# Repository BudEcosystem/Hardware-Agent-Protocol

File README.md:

# Bud Hardware Model Standard

An independent research and design project for agents operating physical devices, from tiny microcontrollers and microscope retrofits to instrument fleets and industrial cells. Intended agent host: the adjacent `Bud-Meta-Harness` repository. This project is **not an implementation of Anthropic's unpublished MHS specification**.

## BHMS: the protocol, SDKs and tools

BHMS (Bud HMS, protocol version `2026-11-15`, with `2026-11-13` compatibility) is the protocol this research produced: JSON-RPC 2.0 in the shape of MCP,
for AI agents, programs and people that discover, observe and operate physical devices, with durable idempotent
operations, honest evidence labels, leases with fencing, unknown outcomes that are never guessed, and a stop that never
waits. It is tested against simulated devices and host-built firmware; no physical device has been validated yet.

- **Start here:** [developer documentation](docs/bhms/index.md), [quickstart](docs/bhms/quickstart.md) (a device server,
  Claude through MCP, an OpenAI model, a gateway; every step executed by the test suite), [concepts](docs/bhms/concepts.md).
- **Specification:** [`spec/bhms`](spec/bhms/README.md) (chapters 01 to 15, JSON Schema, examples, conformance index).
- **Code:** Python SDK, gateway, agent bridges and conformance runner in [`sdk/python`](sdk/python/pyproject.toml)
  (`pip install -e 'sdk/python[mcp,openai]'`, then `bhms --help`); [`sdk/typescript`](sdk/typescript/README.md);
  the C library and Arduino wrapper for microcontrollers in [`sdk/c`](sdk/c/README.md); SimLab, a simulated laboratory
  with real-protocol instruments, in [`simlab`](simlab/README.md); the open BHMS Arm in [`hardware/actuator`](hardware/actuator/README.md).
- **Changes and numbers:** [migration notes](docs/bhms/migration.md), [performance](docs/bhms/performance.md),
  [final validation report](docs/bhms/validation-report.md).

The rest of this README describes the earlier HMS research runtime (`hms/`, `protocol/`, `tests/`) and its retained
evidence.

**Current status:** the executable local simulation runtime combines the registry, admission policy, durable journal, checked API/SDK and `hctl` CLI. A native Harness overlay exercises real tool/PTC calls at a pinned commit in an isolated checkout, with full artifact and aggregate builds passing. A local MCP projection supports current and legacy clients over stdio. The runtime can mount multiple local and compact C simulation routes under one authority, with immutable operation routing, durable mappings, receipt reconciliation and host-process recovery. An explicitly selected shared-board GPIO/PWM simulation also uses the same public tools and resource admission. Primary-source research and checked WoT descriptions support the design. Real adapters, complete commissioned firmware, production Harness integration and physical validation remain unfinished. [Progress and requirement audit](PROGRESS.md) records the evidence and remaining work.

The [qualification libraries are installed in the main project](artifacts/implementation/runtime-qualification-package/README.md):
40 additional host modules and 42 package files retain the exact qualified source.
The installed identity inspection matches the successful candidate, including its
267-file worker image. A new full public run passes **866 tests**, preserving all
861 prior tests and adding five original vault commit checks, with **244 stable
inputs** including native C and binary files. [Library guide](docs/qualification-libraries.md).
Public qualification/PAT service mounting, prompt learning and physical providers
remain unfinished; the native supervisor retains its explicit host/ABI profile.

An isolated [intent handoff](artifacts/implementation/prompt-intent-handoff/README.md)
now retains natural-language intent revisions and checked agent proposals, with
22 focused tests passing. It preserves exact replay and refuses stale proposals;
it does not qualify, promote or execute them. The [source audit](artifacts/design/prompt-intent-handoff/README.md)
records the remaining learning/qualification and Harness integration gaps.

The [selection-reuse host candidate](artifacts/implementation/standing-host-selection-reuse/RESULTS.md)
passes 34 compiler comparisons and nine native management/freshness cases.
Private compilation reuses one freshly validated snapshot within the call,
reducing installation validations from five to one while preserving current
authority and final guards. Its [subsequent full-capacity attempt](artifacts/implementation/standing-host-selection-capacity/RESULTS.md)
still hits the thirty-second limit, retaining 110 settled and one prepared START.
Full capacity and performance benefit remain open.
The [phase-kernel firmware](artifacts/implementation/standing-endpoint-phase-kernels/RESULTS.md)
passes six complete differential traces and saves another 716 flash bytes.
Its failed link charges 39,186 flash bytes, exceeding the original AVR application
allowance by 6,930 bytes; no valid target image or complete stack proof exists.

The isolated [Arduino runtime integration](artifacts/implementation/avr-link-integration/README.md)
joins the finite endpoint, serial receive/transmit, Timer1 and durable boot
reservation. Eleven integrated register-model cases pass normally and under
ASan/UBSan, alongside the original endpoint suite. The combined ATmega328P image
cross-links at 21,778 flash bytes and 1,343 static SRAM bytes. These are model
and build results; target execution, physical I/O and persistent applications
remain unfinished.

The isolated [compact-bitmap storage candidate](artifacts/implementation/compact-bitmap-store/README.md)
passes 329 focused checks and a paired 426-operation screen while preserving
current identity checks and full durability barriers. Its full 4,270-file writer
still times out at the original 180-second limit. A read-only audit verifies
35 retained images, including 1,814 complete files and all 169 directories in
the interrupted writer. The candidate remains unadopted; all 244 public inputs
retain the existing 866-test baseline. The preceding
[attribution](artifacts/verification/full-storage-attribution/README.md) and new
[existing-state overwrite review](artifacts/verification/state-overwrite-hypothesis/README.md)
retain the evidence and next hypothesis. An [existing-state replacement draft](artifacts/implementation/existing-state-replacement/STATUS.md)
has source only; its delegated preparation was stopped by automatic review and
no model or replay was executed.

Device I/O, drivers and the intelligence hub share one
[managed resource graph](docs/io-driver-hub-control.md) and an explicit
[I/O and driver boundary](spec/12-io-driver-boundary.md). New acquisition,
configuration and native queue handoff retain their actual effects and authority.
The isolated
[hub recovery increment](artifacts/implementation/owned-hub-recovery/RESULTS-REVIEW.md)
passes five groups covering interrupted terminal writes, retained handles,
typed computation, replay and limits. A separate [owner-death harness](artifacts/implementation/owned-hub-crash-harness/README.md)
passes twelve actual process-death checkpoints, preserving six not_started,
three unknown and three completed outcomes without relaunching historical work.
The [writer-deferral controls](artifacts/implementation/owned-hub-writer-deferral/RESULTS-REVIEW.md)
add three deliberate held-writer cases after leader exit and owner death. Recovery
retains admission until the writer settles, then records unknown; independent
auditing verifies the retained rows, leases and all ten controlled process reaps.
It is not yet a public mount or a qualified GB10/GPU/driver/device provider.

The [standing endpoint design](artifacts/design/standing-endpoint-programs/README.md)
specifies local triggers, feedback, renewable authority, retained evidence and
shared I/O ownership for a narrow Arduino controller. The [fit candidate](artifacts/implementation/standing-endpoint-fit/RESULTS-REVIEW.md)
passes thirteen native cases / 673 assertions in both normal and sanitizer builds,
plus the finite endpoint and runtime regressions. It reduces flash load by 582
bytes and meets the 160-byte static-growth allowance. Its ATmega328P link still
fails: 43,064 flash-load bytes exceed physical flash by 10,296 bytes.
Target fit, complete learning, installation and physical qualification remain
unfinished. The [prompt-to-PAT contract](docs/prompt-to-pat.md) keeps planning,
perception and evidence failures distinct.

The subsequent [LTO profile](artifacts/implementation/standing-endpoint-lto/RESULTS-REVIEW.md)
compiles all twelve units but still fails linking: **41,892 flash-load bytes**,
or **9,124 bytes over physical flash**. Static SRAM remains 1,503 bytes. The
1,172-byte reduction includes a stronger explicit symbol-retention policy.
Both attempts and 32 command reaps are audited; no valid ELF or final combined
stack/timing proof exists. The unchanged native source retains its parent tests.

The [copy/boundary successor](artifacts/implementation/standing-endpoint-copy-boundary/RESULTS-REVIEW.md)
passes fourteen standing cases / 766 assertions in normal and sanitizer builds,
plus the finite/runtime regressions. Flash load is now 41,810 bytes, still 9,042
over physical flash. Its generated standing branch retains six caller bytes
instead of 101; complete stack/ISR analysis and target fit remain open.
The subsequent [shared-kernel refactor](artifacts/implementation/standing-endpoint-shared-kernel/RESULTS.md)
implements shared time/serialization work across both protocols. Four complete
baseline/candidate traces match, including 475 new boundary assertions; numeric
controls pass 13,014 assertions in each mode. Flash load falls by 1,908 bytes to
39,902, still 7,134 above physical flash. All 50 command reaps are audited.
There is no valid target ELF or complete stack/timing qualification.

The [host deployment integration plan](artifacts/design/standing-host-deployment/HOST-DEPLOYMENT-PLAN.md)
maps the remaining journal, shared ownership, version-2 transport, durable
commit-before-ACK collection and standing PAT work to existing source. Its isolated
implementation now passes [twenty native host cases / 173 checks](artifacts/implementation/standing-host-deployment/RESULTS-REVIEW.md).
It includes one shared finite/standing authority, an original-evaluator-backed
literal PAT path and a 16 MiB all-writer logical partition. Prepared-only recovery,
durable reply disputes, policy replacement and separate REVOKE uncertainty have
controls. A separate [thirteen-cut owner-death increment](artifacts/implementation/standing-host-owner-death/RESULTS-REVIEW.md)
now passes with the native endpoint surviving each killed host. Historical
possible effects are not resent, and exact terminal evidence gates claim release.
The [boundary successor](artifacts/implementation/standing-host-boundaries/RESULTS.md)
adds eight authority/replay and ten synchronous storage-failure controls that
pass. Its mutation-capacity attempt reaches the unchanged 30-second wall limit
after 68 never-handed-off mutations; the failed attempt is retained and the
remaining matrix is unexecuted. Full capacity, broader failure modes, public mounting and physical drivers remain
open; these results are partial validation of the fixed synthetic profile.

The [PAT foundation](artifacts/implementation/runtime-pat-foundation/README.md)
provides commit-time validation, compiler identity and static resource checks.
The new [statement-cache integration](artifacts/implementation/pat-statement-cache/README.md)
passes **nineteen catalog controls and the complete thirty-case worker → vault →
catalog → PAT application flow**. One simulated application completes once, with
original-key replay, configuration drift refusal and cold history intact.

The worker completes in about 57.7 seconds under the original 60-second limit;
the parent completes in 141.1 seconds under 180 seconds. The only production
change is a 256-statement authority Journal cache. That same edit is now in the
public runtime, where the preceding full run passed **861 tests** with 161
stable inputs. The subsequent library installation above extends that coverage.
Public qualification, prompt learning and physical device/driver/hub providers
remain unfinished. One successful local run does not qualify deployment timing.

The preceding [local comparison](artifacts/verification/pat-statement-cache-evaluation/README.md)
passes 62 checks and observes 38.46% lower median capture CPU; this is not a
whole-worker speedup claim. The [binding review](research/host-contract/sqlite-cache-binding/README.md)
adds 4,025 fully read LF lines and records cursor/memory lifetime constraints.

The [current worker diagnostic](artifacts/verification/qualification-current-profile/README.md)
retains a complete-matrix request and the original limits. It stops at the deadline
with 21 case manifests, records current SQLite/validation/durability costs and
publishes no qualification or application. A separate encoder experiment passes
1,875 semantic cases but is not adopted because its timing benefit is inconsistent.
The subsequent [SQL metadata experiment](artifacts/verification/pat-sql-metadata-evaluation/README.md)
matches 410 differential cases but is also unadopted: fewer queries produce about
6.3% higher median CPU in the fixed local comparison. The
[statement-cache review](research/host-contract/sqlite-statement-cache/README.md)
adds 477 fully read LF lines and identifies a separate hypothesis to measure:
164 distinct authority capture statements versus the installed 128-statement
default. This static count does not establish cache misses or a timeout cause.

The [qualification package candidate](artifacts/implementation/qualification-package/README.md)
has explicit package imports and a pinned worker image. Import and identity checks
pass, but its actual thirty-case qualification hit the original worker deadline:
25 case manifests were retained, with no evidence publication or PAT application.
The failure is preserved separately from catalog controls; public integration
remains unfinished. That failed attempt remains retained; the later cache candidate above completes the same matrix.

The earlier isolated [authority-vault catalog](artifacts/implementation/pat-vault-catalog/README.md)
passes 19 controls and the complete thirty-case worker → vault → catalog → PAT
application flow. One simulated GPIO application completes exactly once; original-key
history survives configuration drift and cold vault/bridge reconstruction. Complete
candidate evidence and current device/driver applicability are checked through
admission commit. Public integration, prompt learning and physical device, driver
and intelligence-hub providers remain unfinished.

The preceding isolated [vault batch candidate](artifacts/implementation/pat-vault-batch/README.md)
passes 60 controls for complete bounded evidence views and their admission-commit
checks. Missing batch members refuse the view; expiry rolls back admission, while
post-commit lease failure retains original-key replay. Its distinct catalog mount
is now connected in the isolated profile above; the full learning loop and physical
providers remain unfinished.

The preceding isolated [business commit candidate](artifacts/implementation/pat-business-precommit/README.md)
passes 51 controls for final evidence checks, rollback, clock-floor preservation
and original-key replay after lost commit replies. It adds the transaction boundary
needed by the independent evidence vault; the bounded catalog evidence view,
public integration and physical providers remain unfinished.

Durable ordered procedures coordinate those routes with atomic child admission,
explicit restart continuation and checked CLI/MCP access. The latest full run
passes **861 tests**, with all 161 inputs and compiler identity unchanged.
The previous 748-test result remains an immutable historical baseline.
The earlier 747-test run retains its status-read timeout. A controlled reproduction
and five passing transport tests verify the test-only polling correction within
the original deadline, without mutation retries. Earlier passing and failed runs
remain preserved. The new
[PAT simulation qualification components](docs/pat-simulation-qualification.md)
include closed configuration/domain contracts, shared environment extraction,
an executable isolated fan worker, a catalog evidence gate and a bounded evidence
reducer/store. The corrected store/hook integration passes 46 focused tests with
fresh worker outputs. Later isolated durable supervision and recorded I/O catalog
integration are verified below; the public qualification service remains unfinished.
The pure I/O resource topology library now passes 21 focused tests;
resource admission and the evidence memo are now integrated as libraries, with
corrected compiler dependency identity. Their focused checks pass 32 and 77 tests;
the new full runtime check includes these libraries alongside the topology,
evidence store and evaluation-integrity fixes. A separate synthetic GPIO/PWM
provider is now [mounted through the public tools](docs/io-simulation.md).
Its final four real CLI/MCP transport cases pass after retained failed37 and
failed52 attempts exposed two integration defects and an incorrect resume-test
expectation. Physical providers and executed driver/hub lifecycle control remain
further work.
[Typed PAT compilation and a trusted local promotion catalog](docs/pat-foundation.md)
and [deterministic selection with atomic instances](docs/pat-execution.md)
now extend that foundation as host libraries. A targeted
[compact admission refresh](docs/compact-admission-refresh.md) addresses reproduced
presence expiry without changing the original request bounds; all 25 focused
admission tests pass within that full run. Prompt-driven applications that learn into deterministic
Programs as Tools, and control spanning device I/O, drivers and intelligence-hub
resources, are core requirements with explicit designs; their full implementation
and physical qualification remain open. Historical Harness runs retain their
exact earlier runtime snapshots.

The isolated [recorded I/O catalog integration](artifacts/implementation/pat-io-definition-build/README.md)
passes 21 pure controls and the actual complete 30-case worker/import/catalog/PAT
application/replay scope. Original-key replay adds no effect, configuration drift
refuses fresh reuse, and cold historical replay survives a session change. Earlier
failed scopes remain preserved. Protected control capacity and public mounting
remain unfinished; this is simulated-device evidence.

The [control-storage review](docs/control-storage.md) adds five passing bounded
SQLite experiments and an unchanged-state allocation audit. It specifies separate
evidence/control storage and capacity owed to admitted work. The corresponding
production profile and actual capacity provider remain to be implemented.

An isolated [immutable evidence vault](artifacts/implementation/pat-evidence-vault/README.md)
now preserves the complete retained I/O dataset in a separately capped database.
All 22 distinct methods have passing receipts on identical production code, with
startup and test-assertion failures retained. An [authority-publication candidate](artifacts/implementation/pat-vault-authority/README.md)
now binds that vault to an actual runtime authority and records original import
intents and manifest references. All [25 selected current-production controls](artifacts/verification/pat-vault-authority-controls/README.md)
now pass in separate scopes, with interrupted attempts and the earlier aggregate
failure retained. Actual-run validation through this profile, catalog integration,
public mounting and backed control capacity remain unfinished.
The [fresh actual trial](artifacts/implementation/pat-vault-original-run/README.md)
hit its original worker deadline before import; its partial capture and unknown
worker outcome remain retained for diagnosis.

A [bounded current-worker profile](artifacts/verification/pat-vault-worker-profile/README.md)
now identifies repeated validation/serialization work for evaluation. Its own
original scope also stopped at the unchanged deadline; all retained bytes and
source databases pass the read-only audit. It establishes neither a timeout cause
nor a complete import, and introduces no production change.

A [pure validator evaluation](artifacts/verification/pat-validation-walk-evaluation/README.md)
passes 468 differential cases. Its small, inconsistent timing improvement is
insufficient to adopt it as a deadline correction; production stays unchanged.

The subsequent [one-call topology/proof candidate](artifacts/implementation/pat-io-proof-batch/README.md)
passes 63 pure controls and reduces repeated validation in definition building.
Its full actual trial still reaches the unchanged worker deadline before import;
it remains isolated and does not qualify the end-to-end path. Original results and
verified retained copies are preserved, including the later loss of temporary trees.

A [whole-worker accounting diagnostic](artifacts/verification/pat-worker-accounting/README.md)
now separates parent and child resource use without changing the project or worker
code. Fifteen observer controls pass. The actual scope still reaches the original
deadline with 25 retained case manifests and no import. During its roughly
60-second worker interval, parent and child use 18.45 and 36.58 CPU seconds.
The audit verifies all retained bytes and original launch association; the next
investigation is parent monitoring cost, with no established single timeout cause.

The [retention-scan comparison](artifacts/verification/pat-retention-scan-cost/README.md)
now verifies 72 read-only scans of the original retained tree. A separate
[native host prototype](artifacts/verification/pat-native-retention-prototype/README.md)
passes 20 differential controls and five syscall scopes, with roughly 61% lower
median scan CPU time in fixed local pairs. Original metadata remains unchanged.
The helper is not integrated; full worker/import qualification remains required.

The subsequent [in-process native binding](artifacts/verification/pat-native-retention-binding/README.md)
passes 43 production-build controls, 20 separate instrumented controls and three
actual syscall scopes. It preserves signal exceptions and descriptor cleanup and
adds opened-directory identity checks. It remains isolated, with no new whole-worker
performance or qualification result. Physical I/O, driver and hub providers remain
required parts of the system.

The [isolated supervisor integration](artifacts/implementation/pat-native-supervisor/README.md)
now loads the verified scanner through a sealed memory image. Six loader scopes
and sixteen audit-guard controls pass. The complete actual worker still reaches
its original deadline before import, leaving fifteen manifests and interrupted
effects unknown. All retained state and source identities are verified; no
whole-worker speedup, public adoption or complete PAT qualification is claimed.

The subsequent [native worker accounting diagnostic](artifacts/verification/pat-native-worker-accounting/README.md)
passes 21 pure controls with unchanged project code. Its full trial reaches the
original deadline with twenty-nine manifests and no import. It measures 10.79
supervisor and 35.85 worker CPU seconds, and verifies the original launch and all
retained state without opening interrupted case databases. Qualification remains
failed; exact canonical-serialization evaluation is the next proposed improvement.
Four previously partial API texts are now fully read in a retained overlay.

The latest [guarded canonicalization candidate](artifacts/implementation/pat-integer-canonical/README.md)
passes the **complete original thirty-case worker and authority-vault import**,
including original-key replay and cold-vault history after configuration drift,
within the unchanged limits. It passes 1,668 pure differential cases and nine
public contract tests. The read-only audit verifies every retained vault body and
its original association. This remains an isolated simulation candidate; the
distinct vault catalog profile, public mounting and backed capacity are next.

## Start here

- [Scope and completion requirements](spec/00-scope.md)
- [Architecture and foundational command interface](spec/01-architecture.md)
- [Execution, state, cancellation and recovery semantics](spec/02-execution.md)
- [Registry, tool manager, runtime and performance](spec/03-registry-runtime.md)
- [Home, scientific and manufacturing scenarios](spec/04-scenarios.md)
- [WoT description profile and execution boundary](spec/05-description-profile.md)
- [Workflow, material identity and recovery](spec/06-workflows-materials.md)
- [Constrained endpoint binding](spec/07-constrained-binding.md) and [serial codec](protocol/serial/README.md)
- [Host invocation, identity and durable journal profile](spec/08-host-contract.md)
- [Local registry and simulation runtime](spec/09-local-runtime.md) and [runnable CLI walkthrough](docs/local-control.md)
- [Checked local API contracts and SDK](spec/10-local-api-contracts.md)
- [Experimental compact endpoint wire/state profile](spec/11-endpoint-wire.md) and [implementation/verification](protocol/endpoint/README.md)
- [Device I/O, driver lifecycle and intelligence-hub boundary](spec/12-io-driver-boundary.md)
- [Durable compact host binding and recovery](docs/compact-host-binding.md)
- [Multiple installed simulation adapters](docs/multi-adapter-runtime.md)
- [Shared-board GPIO/PWM simulation and startup](docs/io-simulation.md)
- [Local MCP tools and interoperability evidence](docs/mcp-integration.md)
- [Platform primitives and finite boot reservations](protocol/platform/README.md)
- [Microscope knob retrofit](docs/microscope-retrofit.md)
- [Bud Meta Harness integration](docs/harness-integration.md)
- [Native Harness overlay and frozen 315-test runtime verification](integration/harness/multi-adapter/README.md)
- [Conformance and physical validation plan](docs/conformance-plan.md)

## Research

- [Official MHS source findings and independent implementation critique](research/mhs/notes/findings.md)
- [Protocol landscape](docs/protocol-landscape.md) and [corpus notes](research/protocols/README.md)
- [WoT reuse decision](docs/wot-reuse-decision.md) and [MQTT/Sparkplug binding requirements](docs/transport-guarantees.md)
- [Physical-AI architectures](docs/physical-ai-landscape.md) and [reading notes](research/physical-ai/notes/reading-notes.md)
- [Learned-control deployment profile](docs/learned-control-profile.md) and [GR00T/OpenVLA full review](research/physical-ai/notes/vla-full-review.md)
- [Laboratory corpus](research/laboratory/README.md) and [SiLA/Bluesky/LabOP binding requirements](docs/laboratory-bindings.md)
- [Description/profile review and repairs](docs/profile-review.md)
- [Constrained protocol corpus](research/constrained/README.md) and [embedded implementation evidence](docs/embedded-evidence.md)
- [Planning and skill grounding](docs/planning-and-grounding.md), [planning corpus](research/planning/README.md), and [Modbus/SCPI bindings](docs/instrumentation-bindings.md)
- [Prompt-to-PAT learning and deterministic reuse](docs/prompt-to-pat.md), [bounded procedures](docs/bounded-procedures.md), and [device I/O, driver and hub control](docs/io-driver-hub-control.md)
- [Executable PAT qualification components and their limits](docs/pat-simulation-qualification.md)
- [Host persistence evidence](research/host-contract/README.md) and [AVR target build/UART review](research/constrained/avr/notes/target-build-and-uart-review.md)
- [Home Assistant/ESPHome binding evidence](docs/home-bindings.md), [OSCORE security binding](docs/oscore-binding.md), and [EDHOC full review](docs/edhoc-binding.md)
- [Observe/Blockwise/reliable-CoAP analysis](docs/coap-streaming-binding.md), [feedback and spatial planning](docs/planning-continuation.md), and [local timing measurements](docs/local-performance.md)
- [OPC UA industrial binding review](docs/opcua-binding.md) and [MCP specification corpus](research/mcp/README.md)
- [Current LwM2M Core/Transport review](docs/lwm2m-current-binding.md) and [microscope controller evidence](docs/microscope-controller-binding.md)
- [WoT Architecture full reading and binding analysis](docs/wot-architecture-binding.md)
- [AVR/RP2040 clock, boot and storage evidence](docs/clock-boot-platform.md)
- [Original AVR Timer1 clock implementation and checks](docs/avr-clock-implementation.md), and [full Q-Block review](docs/qblock-binding.md)
- [GB10/DGX Spark hub deployment evidence](docs/gb10-deployment-evidence.md)
- [Search and full-reading backlog](research/PLAN.md)

Raw articles, papers and pinned source checkouts/snapshots are local under `research/`. Acquisition manifests and reading logs are separate: downloaded is not synonymous with read. Source licenses remain with their owners. The small audited JCS library is intentionally [vendored](hms/_vendor/README.md); other research checkouts are reference material. Large model weights, training datasets, recursive submodules and complete Git history have not been acquired.

## Check the draft artifacts

Python 3, `requests`, `beautifulsoup4` and `jsonschema` are used by the local research utilities. The complete Python test suite additionally uses installed MCP SDK 1.26.0 and AnyIO as tester dependencies; the production MCP projection does not depend on that SDK. Native C framing tests additionally require GCC; the stress check uses address/undefined-behavior sanitizers. PDF extraction uses `pdftotext`. These were available in the working environment; reproducible dependency locking is still outstanding.

```sh
python3 scripts/audit_corpus.py
python3 scripts/check_descriptions.py
python3 scripts/check_wot_profile.py
python3 scripts/check_endpoint_scenarios.py
python3 -m unittest discover -s tests -v
python3 scripts/check_serial_native.py
python3 scripts/check_endpoint_native.py
python3 scripts/check_endpoint_integration.py
python3 scripts/check_compact_mcp.py
python3 scripts/check_boot_epoch.py
python3 scripts/check_avr_eeprom.py
python3 scripts/check_host_journal.py
python3 scripts/check_runtime.py
```

The JSON descriptions in `examples/` and `examples/wot/` are synthetic, uncommissioned design examples. WoT TD 1.1 is the chosen host description direction; the action forms now project the full host envelope. Static fixtures pin their original physical-contract files, while executable simulation types use a separately versioned type-bundle digest. Example HTTPS forms are placeholders, not installed endpoints. The CLI uses an authenticated local Unix socket; all processes with one Unix UID share a principal. Checks cover corpus integrity, descriptions, framing, request identity, simulated execution and crash recovery. They do not establish physical behavior, timing or complete protocol conformance. The [AVR build instructions](research/constrained/avr/notes/target-build-and-uart-review.md) reproduce its component-only footprint without flashing hardware.

The [endpoint build](protocol/endpoint/README.md) additionally cross-links the executor, framing and synthetic callbacks for ATmega328P. Its 15,780-byte flash image, 1,335-byte static RAM allocation and conservative static stack analysis fit the declared planning reservations; no target program ran. Qualified clock/NVM/UART and actual device drivers remain separate work. [Evidence consistency audit](artifacts/verification/endpoint-evidence-audit.json) links the retained source, binary and test receipts.

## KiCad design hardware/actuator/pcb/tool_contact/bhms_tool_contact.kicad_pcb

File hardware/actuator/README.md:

# BHMS Arm — universal actuator hardware

BHMS Arm is a 5-axis desktop arm built from Feetech STS3215 12 V serial
bus servos. It has a quick-change tool flange and four end effectors:

* parallel gripper
* compliant knob turner with an output encoder
* button presser with a force-sensing tip
* slider/rocker pusher

An RP2040 controller board drives the arm. A hardware E-stop cuts the
servo power with no firmware involvement. The arm is the physical
counterpart of the SimLab arm twin: `sim/bhms_arm.xml` is generated from
the same parameters and CAD solids that produce the printed parts.

**Status.** Design only (Task 13a). Nothing has been printed, assembled,
powered or certified, and no PCB has been manufactured.

* CAD, MJCF and PCBs are checked by tools: OpenCASCADE, trimesh, MuJoCo
  4.0.1, KiCad 10.0.6 `kicad-cli`, Freerouting 1.9.0 and the scripted
  checks in this tree. Results are in `docs/design.md` §10.
* Both PCBs are fully routed (the controller needed a scripted completion
  pass after the autorouter, `pcb/finish.py`) with 0 KiCad ERC/DRC errors.
  They have not been reviewed by a person: read `docs/design.md` §12 (O7)
  before ordering. `pcb/build.py fab` refuses to write Gerbers for any
  board that has known open routing (`pcb/<board>/known_open.json`) and
  writes `DO_NOT_FABRICATE.md` instead.
* The arm falls when the E-stop cuts power (no brake): `docs/design.md` §9.
* Firmware (Task 13b): `firmware/` (README.md). Its contract is `firmware/INTERFACE.md`.

| | |
|---|---|
| Reach (shoulder axis → flange) | 400 mm (180 + 140 + 80) |
| Rated load | 250 g carried object, tool excluded, 70 mm beyond the flange, plus the 159 g gripper. Static 2× margin against the enforced servo torque limits at every joint (shoulder 2.06× at its 78 % limit, elbow 3.62×, wrist 4.64×); machined steel shoulder pinion |
| Joints | yaw ±150°, shoulder −20…+95° (3:1), elbow −5…+125° (2:1), wrist pitch ±100°, wrist roll ±150°, plus coupled pitch limits (shoulder+elbow ≤ 175°, elbow+wrist ≤ 165°, sum of all three ≤ 183°; `firmware/INTERFACE.md` §3.2) |
| Tool flange | 3-lug bayonet locked by a +30° wrist roll; 6 pogo contacts: 12 V, GND, bus, AUX1, AUX2, tool ID |
| Controller | RP2040, 16 MB flash, USB-C, 12 V in with fuse/TVS/reverse protection, half-duplex servo bus, INA219 rail sensing, hardware E-stop loop, tool port, RGB LED, SWD |
| Cost (estimate) | see `bom/bom.csv` totals |

## Layout

```
params.py lives in cad/ — every dimension, ratio, limit, servo ID and tool ID
cad/            build123d part modules (cad/parts/*.py), build.py, mesh/clearance/torque checks
cad/out/        STL (committed, each < 2 MiB), STEP (manifest only), parts/assembly/check JSON
sim/            gen_mjcf.py -> bhms_arm*.xml, scene_pick.xml; test_arm.py; results/sim_results.json
pcb/            controller.py, tool_contact.py (circuits + placement), KiCad writers, router glue, DRC
pcb/<board>/    .kicad_sch/.kicad_pcb/.kicad_pro (KiCad 8 format), netlist, reports, fab/ (Gerber, drill, pos)
bom/            build_bom.py -> bom.csv
firmware/       RP2040 firmware: portable core, host simulator and tests, pico-sdk port; INTERFACE.md is the contract
docs/           design.md (requirements, torque budget, safety, decisions), assembly.md, img/
verify.sh       regenerate + verify everything
```

## Regenerate

The worker used for verification had build123d 0.13 / OCP 8.0.1 and
trimesh 5.2 in one venv, MuJoCo 4.0.1 in another, and KiCad 10.0.6
unpacked from the Ubuntu .debs:

```bash
CAD_PY=~/venvs/cad/bin/python SIM_PY=~/venvs/arm/bin/python \
FREEROUTING="xvfb-run -a java -jar freerouting-1.9.0.jar" ./verify.sh
```

With `FREEROUTING` unset (or `SKIP_ROUTE=1`) `verify.sh` imports the
committed Freerouting sessions (`pcb/*/*.ses`) instead of re-routing, which
reproduces the committed boards exactly. A missing `kicad-cli` fails the
run unless `ALLOW_NO_KICAD=1` is set; then the KiCad ERC/DRC/Gerber steps
are reported as SKIPPED in the summary. The interference check uses
`CLEARANCE_JOBS` worker processes (default 6) and takes about 10 minutes.

Each step is also a plain script: `cad/build.py`, `cad/check_meshes.py`,
`cad/check_clearance.py`, `cad/torque_budget.py`, `sim/gen_mjcf.py`,
`sim/test_arm.py`, `pcb/build.py {generate,route,check,fab}` and
`bom/build_bom.py`.

## Using the twin in SimLab

Load `sim/bhms_arm.xml`; it has the gripper. Variants `bhms_arm_<tool>.xml`
carry the other tools. Actuator, joint and sensor names match the
firmware's joint names (`base_yaw`, `shoulder_pitch`, …). Tool TCPs are the
`tcp` site. Keyframe `home` (yaw 0°, shoulder 30°, elbow 90°, wrist 45°, roll 0°) is the pose the
controller reaches after calibration and the rest pose for a normal stop; it satisfies
all joint and coupled limits.

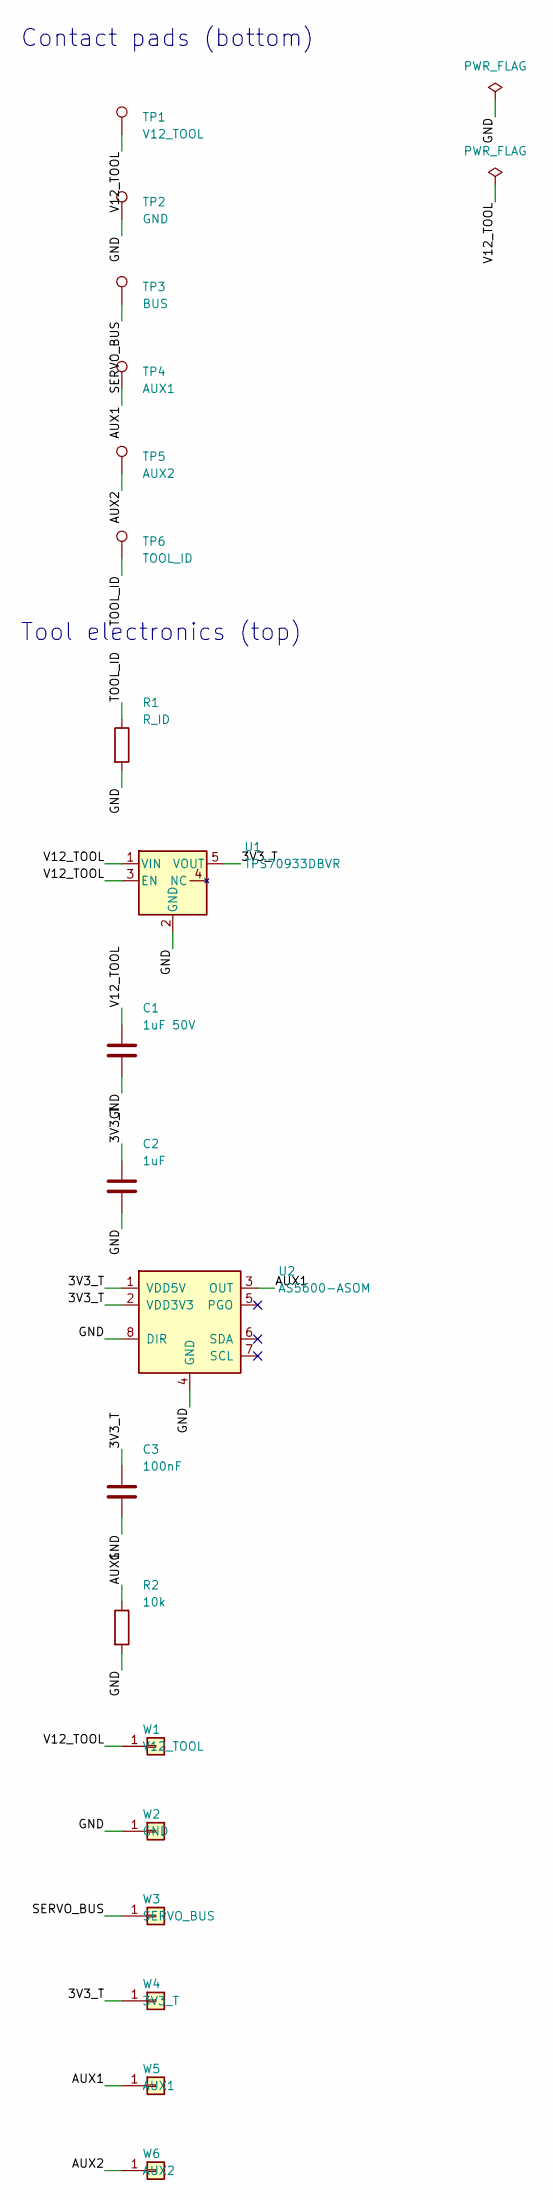
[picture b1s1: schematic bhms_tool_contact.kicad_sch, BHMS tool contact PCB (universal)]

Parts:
C1: 1uF 50V; C_0603_1608Metric; MPN GRM188R61H105KAAL
C2: 1uF; C_0603_1608Metric; MPN GRM188R61H105KAAL
C3: 100nF; C_0603_1608Metric; MPN CL10B104KB8NNNC
R1: R_ID; R_0603_1608Metric; MPN RC0603FR-07xxxL (per tool)
R2: 10k; R_0603_1608Metric; MPN RC0603FR-0710KL
TP1: V12_TOOL; PogoPad_D2.4
TP2: GND; PogoPad_D2.4
TP3: BUS; PogoPad_D2.4
TP4: AUX1; PogoPad_D2.4
TP5: AUX2; PogoPad_D2.4
TP6: TOOL_ID; PogoPad_D2.4
U1: TPS70933DBVR; SOT-23-5; MPN TPS70933DBVR
U2: AS5600-ASOM; SOIC-8_3.9x4.9mm_P1.27mm; MPN AS5600-ASOM
W1: V12_TOOL; WirePad_1.6
W2: GND; WirePad_1.6
W3: SERVO_BUS; WirePad_1.6
W4: 3V3_T; WirePad_1.6
W5: AUX1; WirePad_1.6
W6: AUX2; WirePad_1.6

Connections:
/3V3_T: C2.1, C3.1, U1.5 (VOUT), U2.1 (VDD5V), U2.2 (VDD3V3), W4.1
/AUX1: R2.1, TP4.1, U2.3 (OUT), W5.1
/AUX2: TP5.1, W6.1
/GND: C1.2, C2.2, C3.2, R1.2, R2.2, TP2.1, U1.2 (GND), U2.4 (GND), U2.8 (DIR), W2.1
/SERVO_BUS: TP3.1, W3.1
/TOOL_ID: R1.1, TP6.1
/V12_TOOL: C1.1, TP1.1, U1.1 (VIN), U1.3 (EN), W1.1

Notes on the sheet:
Contact pads (bottom)
Tool electronics (top)

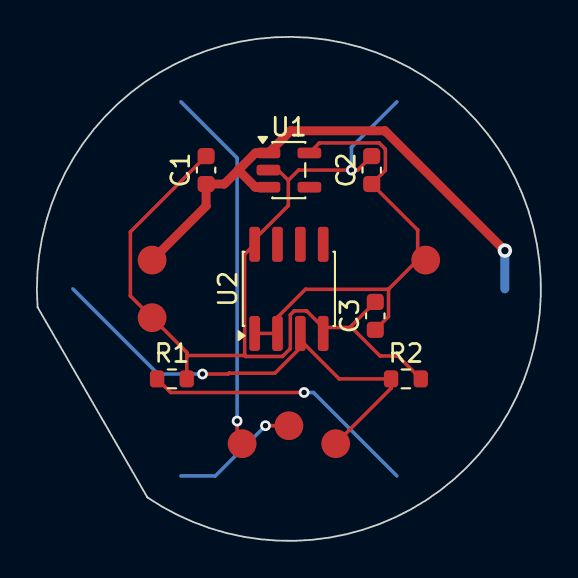
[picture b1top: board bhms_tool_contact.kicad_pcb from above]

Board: 2 copper layers, 28.0 x 28.0 mm, 19 parts (0 on the bottom side), 7 nets.

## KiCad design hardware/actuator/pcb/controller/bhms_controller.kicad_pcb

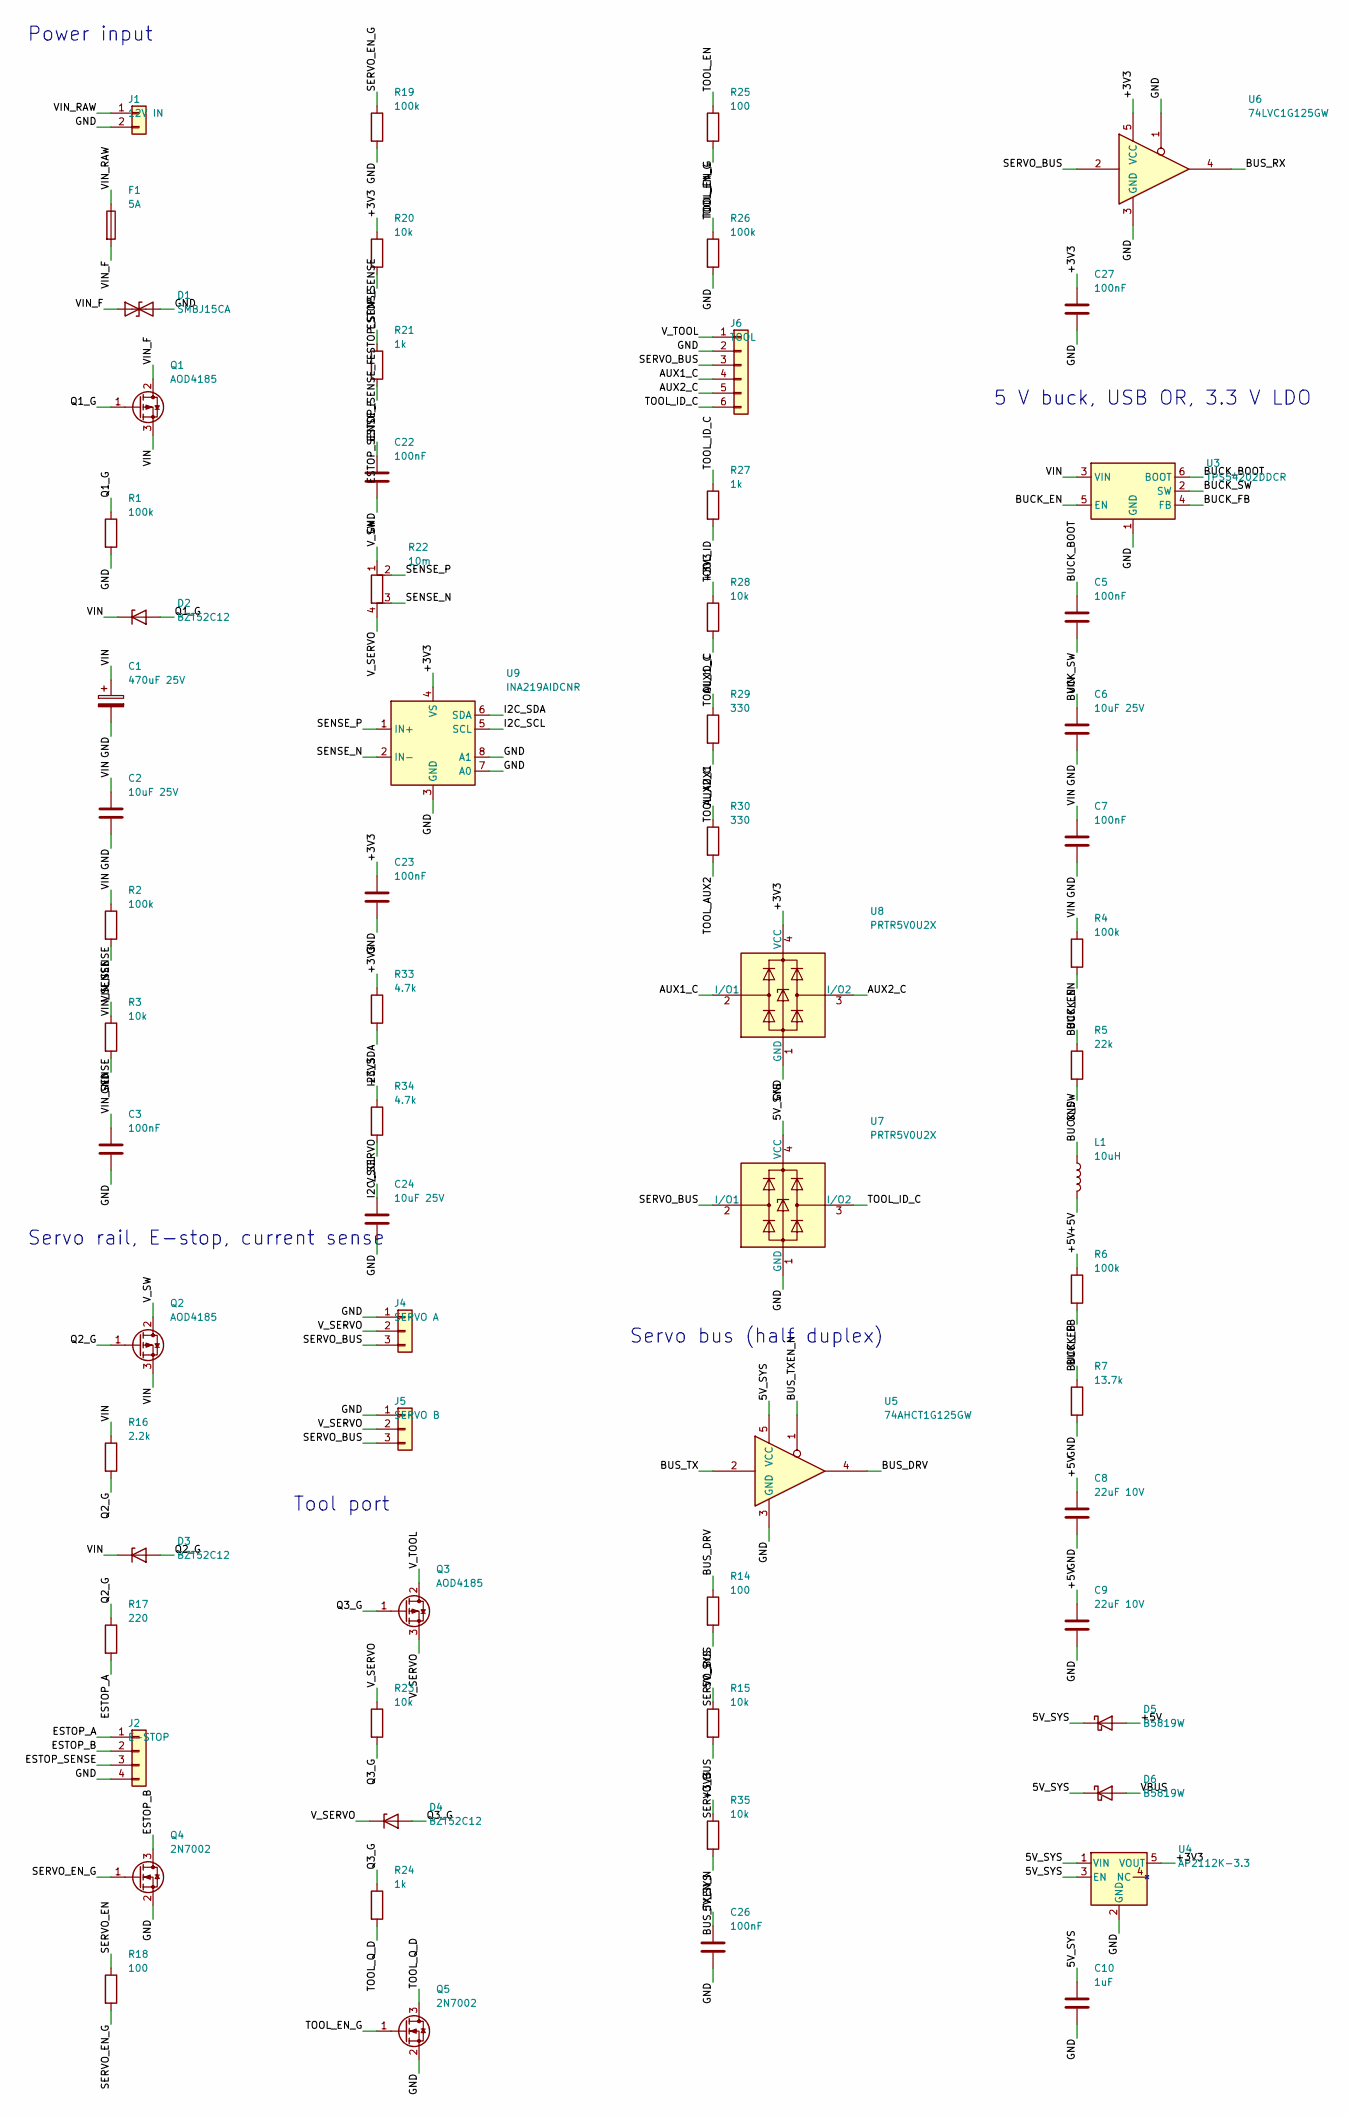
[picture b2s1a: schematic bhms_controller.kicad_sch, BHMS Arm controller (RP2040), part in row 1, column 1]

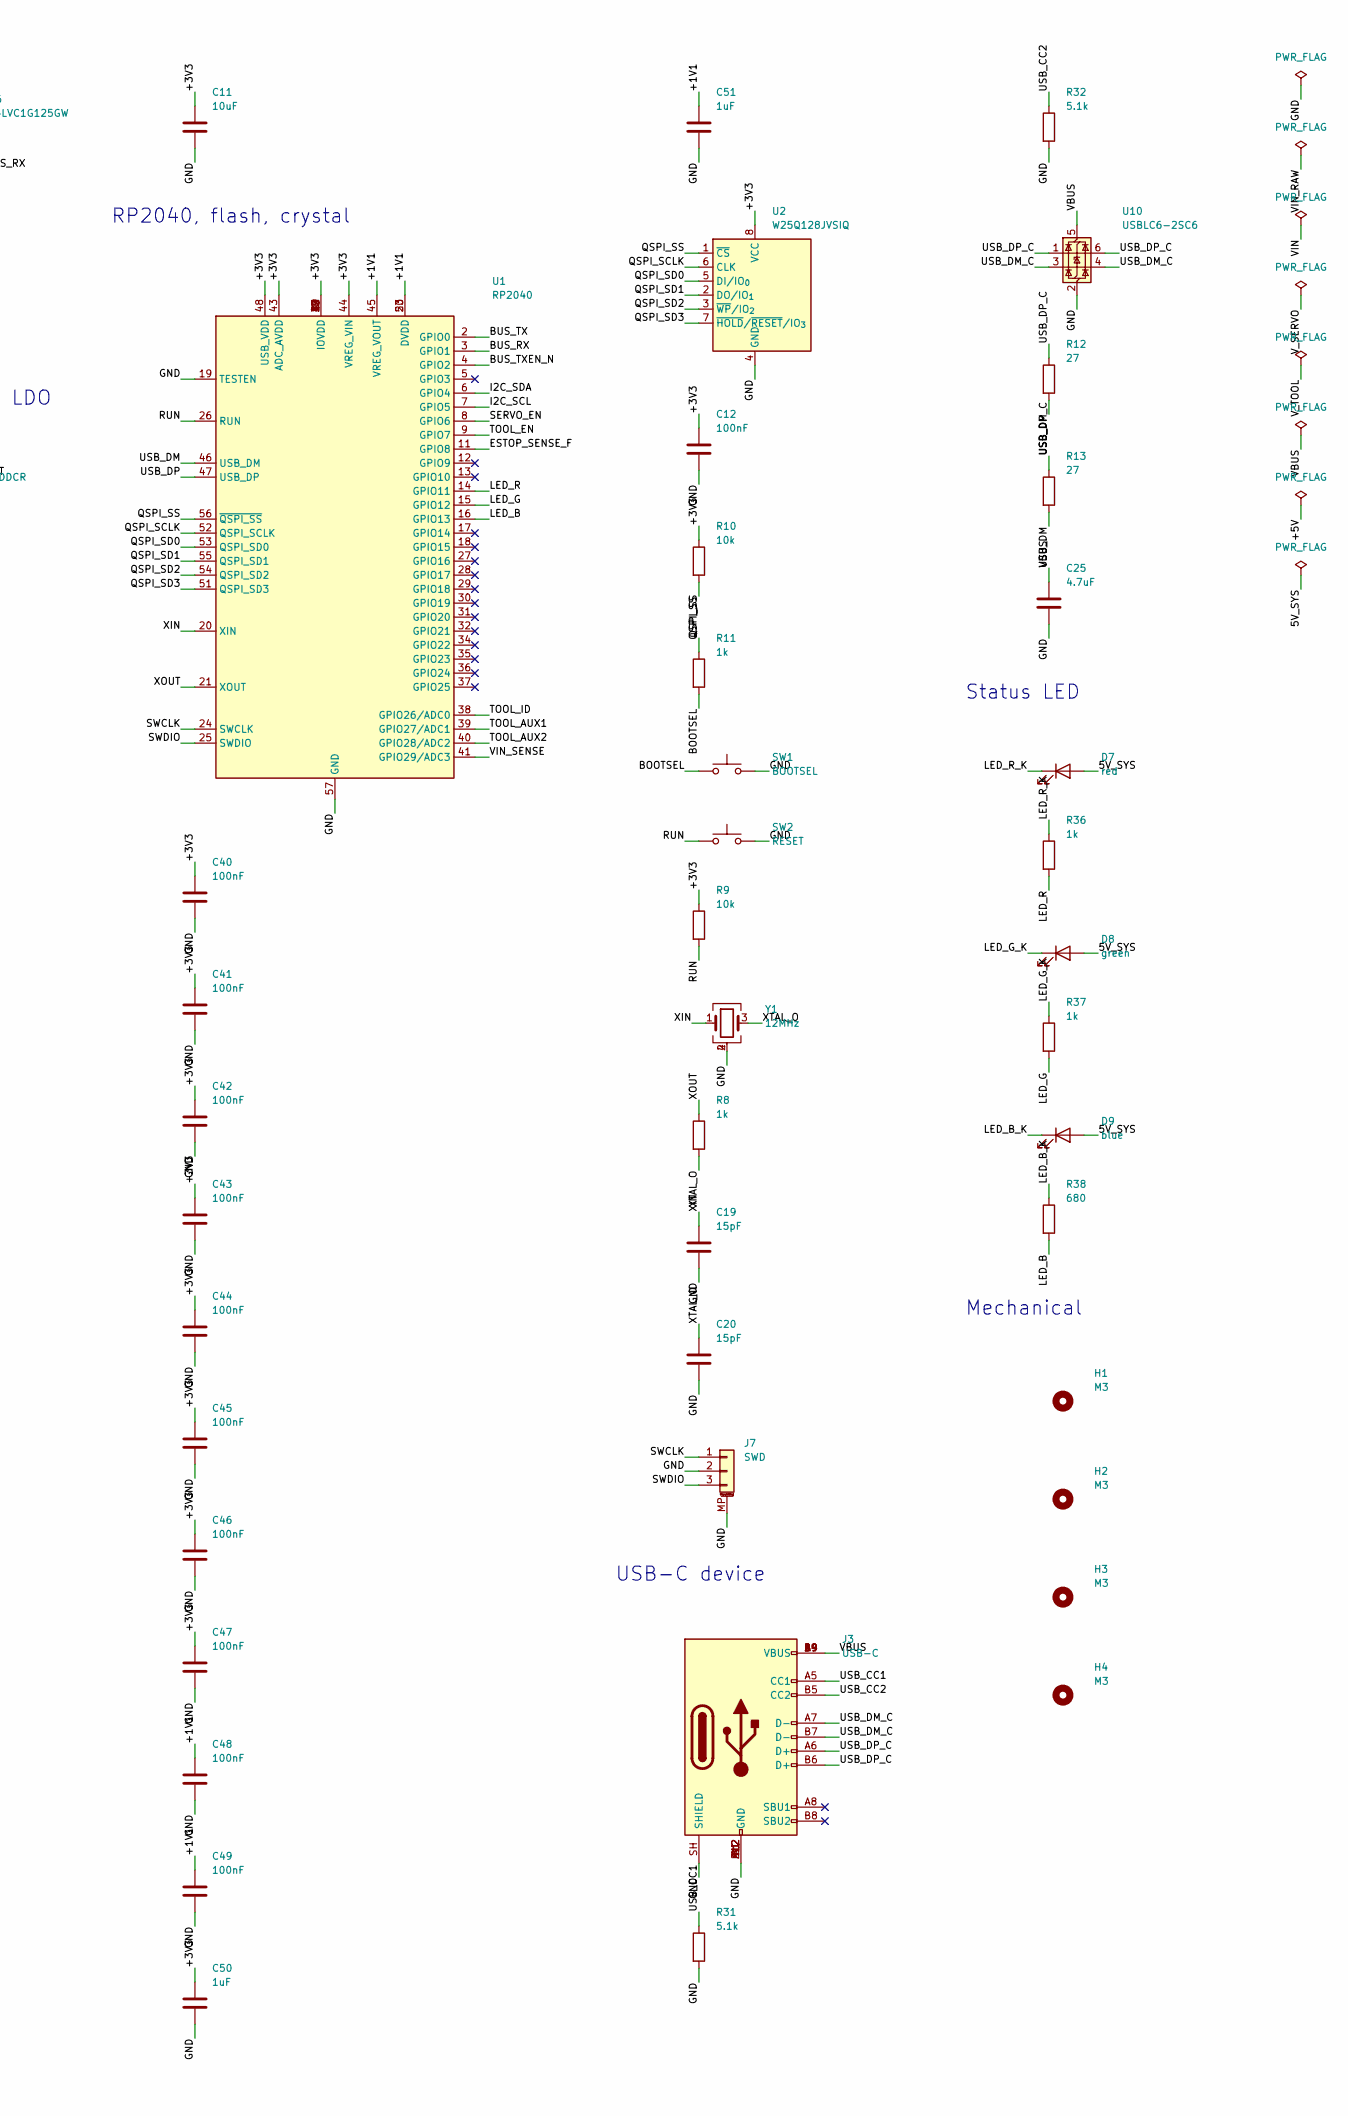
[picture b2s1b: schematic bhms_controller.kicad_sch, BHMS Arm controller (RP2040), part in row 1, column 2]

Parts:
C1: 470uF 25V; CP_Radial_D10.0mm_P5.00mm; MPN EEU-FR1E471
C2, C6, C24: 10uF 25V; C_0805_2012Metric; MPN CL21A106KAYNNNE
C3, C5, C7, C12, C22, C23, C26, C27, C40, C41, C42, C43, C44, C45, C46, C47, C48, C49: 100nF; C_0603_1608Metric; MPN CL10B104KB8NNNC
C8, C9: 22uF 10V; C_0805_2012Metric; MPN GRM21BR61A226ME51L
C10, C50, C51: 1uF; C_0603_1608Metric; MPN CL10A105KB8NNNC
C11: 10uF; C_0805_2012Metric; MPN CL21A106KAYNNNE
C19, C20: 15pF; C_0603_1608Metric; MPN CL10C150JB8NNNC
C25: 4.7uF; C_0603_1608Metric; MPN CL10A475KO8NNNC
D1: SMBJ15CA; D_SMB; MPN SMBJ15CA
D2, D3, D4: BZT52C12; D_SOD-123; MPN BZT52C12-7-F
D5, D6: B5819W; D_SOD-123; MPN B5819W-TP
D7: red; LED_0603_1608Metric; MPN APTD1608LSURCK
D8: green; LED_0603_1608Metric; MPN APTD1608LZGCK
D9: blue; LED_0603_1608Metric; MPN APTD1608LVBC/D
F1: 5A; Fuse_Littelfuse-NANO2-451_453; MPN 0451005.MRL
H1, H2, H3, H4: M3; MountingHole_3.2mm_M3
J1: 12V IN; TerminalBlock_Phoenix_MKDS-1,5-2-5.08_1x02_P5.08mm_Horizont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; MPN 1715721
J2: E-STOP; JST_XH_B4B-XH-A_1x04_P2.50mm_Vertical; MPN B4B-XH-A(LF)(SN)
J3: USB-C; USB_C_Receptacle_GCT_USB4105-xx-A_16P_TopMnt_Horizontal; MPN USB4105-GF-A
J4: SERVO A; Molex_SPOX_5267-03A_1x03_P2.50mm_Vertical; MPN 22035035
J5: SERVO B; Molex_SPOX_5267-03A_1x03_P2.50mm_Vertical; MPN 22035035
J6: TOOL; JST_XH_B6B-XH-A_1x06_P2.50mm_Vertical; MPN B6B-XH-A(LF)(SN)
J7: SWD; JST_SH_SM03B-SRSS-TB_1x03-1MP_P1.00mm_Horizontal; MPN SM03B-SRSS-TB(LF)(SN)
L1: 10uH; L_Bourns_SRN6045TA; MPN SRN6045TA-100M
Q1, Q2, Q3: AOD4185; TO-252-2; MPN AOD4185
Q4, Q5: 2N7002; SOT-23; MPN 2N7002,215
R1, R2, R4, R6, R19, R26: 100k; R_0603_1608Metric; MPN RC0603FR-07100KL
R3, R9, R10, R15, R20, R23, R28, R35: 10k; R_0603_1608Metric; MPN RC0603FR-0710KL
R5: 22k; R_0603_1608Metric; MPN RC0603FR-0722KL
R7: 13.7k; R_0603_1608Metric; MPN RC0603FR-0713K7L
R8, R11, R21, R24, R27, R36, R37: 1k; R_0603_1608Metric; MPN RC0603FR-071KL
R12, R13: 27; R_0603_1608Metric; MPN RC0603FR-0727RL
R14, R18, R25: 100; R_0603_1608Metric; MPN RC0603FR-07100RL
R16: 2.2k; R_0603_1608Metric; MPN RC0603FR-072K2L
R17: 220; R_0603_1608Metric; MPN RC0603FR-07220RL
R22: 10m; R_Shunt_Vishay_WSK2512_6332Metric_T1.19mm; MPN WSK2512R0100FEA
R29, R30: 330; R_0603_1608Metric; MPN RC0603FR-07330RL
R31, R32: 5.1k; R_0603_1608Metric; MPN RC0603FR-075K1L
R33, R34: 4.7k; R_0603_1608Metric; MPN RC0603FR-074K7L
R38: 680; R_0603_1608Metric; MPN RC0603FR-07680RL
SW1: BOOTSEL; SW_SPST_PTS810; MPN PTS810 SJM 250 SMTR LFS
SW2: RESET; SW_SPST_PTS810; MPN PTS810 SJM 250 SMTR LFS
U1: RP2040; QFN-56-1EP_7x7mm_P0.4mm_EP3.2x3.2mm; MPN RP2040
U2: W25Q128JVSIQ; SOIC-8_5.3x5.3mm_P1.27mm; MPN W25Q128JVSIQ
U3: TPS54202DDCR; SOT-23-6; MPN TPS54202DDCR
U4: AP2112K-3.3; SOT-23-5; MPN AP2112K-3.3TRG1
U5: 74AHCT1G125GW; SOT-353_SC-70-5; MPN 74AHCT1G125GW,125
U6: 74LVC1G125GW; SOT-353_SC-70-5; MPN 74LVC1G125GW,125
U7, U8: PRTR5V0U2X; SOT-143; MPN PRTR5V0U2X,215
U9: INA219AIDCNR; SOT-23-8; MPN INA219AIDCNR
U10: USBLC6-2SC6; SOT-23-6; MPN USBLC6-2SC6
Y1: 12MHz; Crystal_SMD_3225-4Pin_3.2x2.5mm; MPN ABM8-272-T3

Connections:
/5V_SYS: C10.1, C26.1, D5.1 (K), D6.1 (K), D7.2 (A), D8.2 (A), D9.2 (A), R15.1, U4.1 (VIN), U4.3 (EN), U5.5 (VCC), U7.4 (VCC)
/+1V1: C48.1, C49.1, C51.1, U1.23 (DVDD), U1.45 (VREG_VOUT), U1.50 (DVDD)
/+3V3: C11.1, C12.1, C23.1, C27.1, C40.1, C41.1, C42.1, C43.1, C44.1, C45.1, C46.1, C47.1, C50.1, R9.1, R10.1, R20.1, R28.1, R33.1, R34.1, R35.1, U1.1 (IOVDD), U1.10 (IOVDD), U1.22 (IOVDD), U1.33 (IOVDD), U1.42 (IOVDD), U1.43 (ADC_AVDD), U1.44 (VREG_VIN), U1.48 (USB_VDD), U1.49 (IOVDD), U2.8 (VCC), U4.5 (VOUT), U6.5 (VCC), U8.4 (VCC), U9.4 (VS)
/+5V: C8.1, C9.1, D5.2 (A), L1.2, R6.1
/AUX1_C: J6.4, R29.1, U8.2 (I/O1)
/AUX2_C: J6.5, R30.1, U8.3 (I/O2)
/BOOTSEL: R11.2, SW1.1
/BUCK_BOOT: C5.1, U3.6 (BOOT)
/BUCK_EN: R4.2, R5.1, U3.5 (EN)
/BUCK_FB: R6.2, R7.1, U3.4 (FB)
/BUCK_SW: C5.2, L1.1, U3.2 (SW)
/BUS_DRV: R14.1, U5.4
/BUS_RX: U1.3 (GPIO1), U6.4
/BUS_TX: U1.2 (GPIO0), U5.2
/BUS_TXEN_N: R35.2, U1.4 (GPIO2), U5.1
/ESTOP_A: J2.1, R17.2
/ESTOP_B: J2.2, Q4.3 (D)
/ESTOP_SENSE: J2.3, R20.2, R21.1
/ESTOP_SENSE_F: C22.1, R21.2, U1.11 (GPIO8)
/GND: C1.2, C2.2, C3.2, C6.2, C7.2, C8.2, C9.2, C10.2, C11.2, C12.2, C19.2, C20.2, C22.2, C23.2, C24.2, C25.2, C26.2, C27.2, C40.2, C41.2, C42.2, C43.2, C44.2, C45.2, C46.2, C47.2, C48.2, C49.2, C50.2, C51.2, D1.2 (A2), J1.2, J2.4, J3.A1 (GND), J3.A12 (GND), J3.B1 (GND), J3.B12 (GND), J3.SH (SHIELD), J4.1, J5.1, J6.2, J7.2, J7.MP (MountPin), Q4.2 (S), Q5.2 (S), R1.2, R3.2, R5.2, R7.2, R19.2, R26.2, R31.2, R32.2, SW1.2, SW2.2, U1.19 (TESTEN), U1.57 (GND), U2.4 (GND), U3.1 (GND), U4.2 (GND), U5.3 (GND), U6.1, U6.3 (GND), U7.1 (GND), U8.1 (GND), U9.3 (GND), U9.7 (A0), U9.8 (A1), U10.2 (GND), Y1.2 (G), Y1.4 (G)
/I2C_SCL: R34.2, U1.7 (GPIO5), U9.5 (SCL)
/I2C_SDA: R33.2, U1.6 (GPIO4), U9.6 (SDA)
/LED_B: R38.2, U1.16 (GPIO13)
/LED_B_K: D9.1 (K), R38.1
/LED_G: R37.2, U1.15 (GPIO12)
/LED_G_K: D8.1 (K), R37.1
/LED_R: R36.2, U1.14 (GPIO11)
/LED_R_K: D7.1 (K), R36.1
/Q1_G: D2.2 (A), Q1.1 (G), R1.1
/Q2_G: D3.2 (A), Q2.1 (G), R16.2, R17.1
/Q3_G: D4.2 (A), Q3.1 (G), R23.2, R24.1
/QSPI_SCLK: U1.52 (QSPI_SCLK), U2.6 (CLK)
/QSPI_SD0: U1.53 (QSPI_SD0), U2.5 (DI/IO_{0})
/QSPI_SD1: U1.55 (QSPI_SD1), U2.2 (DO/IO_{1})
/QSPI_SD2: U1.54 (QSPI_SD2), U2.3 (~WP/IO_{2})
/QSPI_SD3: U1.51 (QSPI_SD3), U2.7 (~HOLD/~RESET/IO_{3})
/QSPI_SS: R10.2, R11.1, U1.56 (~QSPI_SS), U2.1 (~CS)
/RUN: R9.2, SW2.1, U1.26 (RUN)
/SENSE_N: R22.3, U9.2 (IN-)
/SENSE_P: R22.2, U9.1 (IN+)
/SERVO_BUS: J4.3, J5.3, J6.3, R14.2, R15.2, U6.2, U7.2 (I/O1)
/SERVO_EN: R18.1, U1.8 (GPIO6)
/SERVO_EN_G: Q4.1 (G), R18.2, R19.1
/SWCLK: J7.1, U1.24 (SWCLK)
/SWDIO: J7.3, U1.25 (SWDIO)
/TOOL_AUX1: R29.2, U1.39 (GPIO27/ADC1)
/TOOL_AUX2: R30.2, U1.40 (GPIO28/ADC2)
/TOOL_EN: R25.1, U1.9 (GPIO7)
/TOOL_EN_G: Q5.1 (G), R25.2, R26.1
/TOOL_ID: R27.2, U1.38 (GPIO26/ADC0)
/TOOL_ID_C: J6.6, R27.1, R28.2, U7.3 (I/O2)
/TOOL_Q_D: Q5.3 (D), R24.2
/USB_CC1: J3.A5 (CC1), R31.1
/USB_CC2: J3.B5 (CC2), R32.1
/USB_DM: R13.2, U1.46 (USB_DM)
/USB_DM_C: J3.A7 (D-), J3.B7 (D-), R13.1, U10.3 (I/O2), U10.4 (I/O2)
/USB_DP: R12.2, U1.47 (USB_DP)
/USB_DP_C: J3.A6 (D+), J3.B6 (D+), R12.1, U10.1 (I/O1), U10.6 (I/O1)
/VBUS: C25.1, D6.2 (A), J3.A4 (VBUS), J3.A9 (VBUS), J3.B4 (VBUS), J3.B9 (VBUS), U10.5 (VBUS)
/VIN: C1.1, C2.1, C6.1, C7.1, D2.1 (K), D3.1 (K), Q1.3 (S), Q2.3 (S), R2.1, R4.1, R16.1, U3.3 (VIN)
/VIN_F: D1.1 (A1), F1.2, Q1.2 (D)
/VIN_RAW: F1.1, J1.1
/VIN_SENSE: C3.1, R2.2, R3.1, U1.41 (GPIO29/ADC3)
/V_SERVO: C24.1, D4.1 (K), J4.2, J5.2, Q3.3 (S), R22.4, R23.1
/V_SW: Q2.2 (D), R22.1
/V_TOOL: J6.1, Q3.2 (D)
/XIN: C19.1, U1.20 (XIN), Y1.1
/XOUT: R8.1, U1.21 (XOUT)
/XTAL_O: C20.1, R8.2, Y1.3

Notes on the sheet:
Power input
Servo rail, E-stop, current sense
Tool port
Servo bus (half duplex)
5 V buck, USB OR, 3.3 V LDO
RP2040, flash, crystal
USB-C device
Status LED
Mechanical
